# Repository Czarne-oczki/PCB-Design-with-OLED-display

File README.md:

# PCB Design with OLED display
# Overview
I am designing a 2-layer PCB that controls an OLED display via I2C, an SD card via SPI, and using a USB interface.

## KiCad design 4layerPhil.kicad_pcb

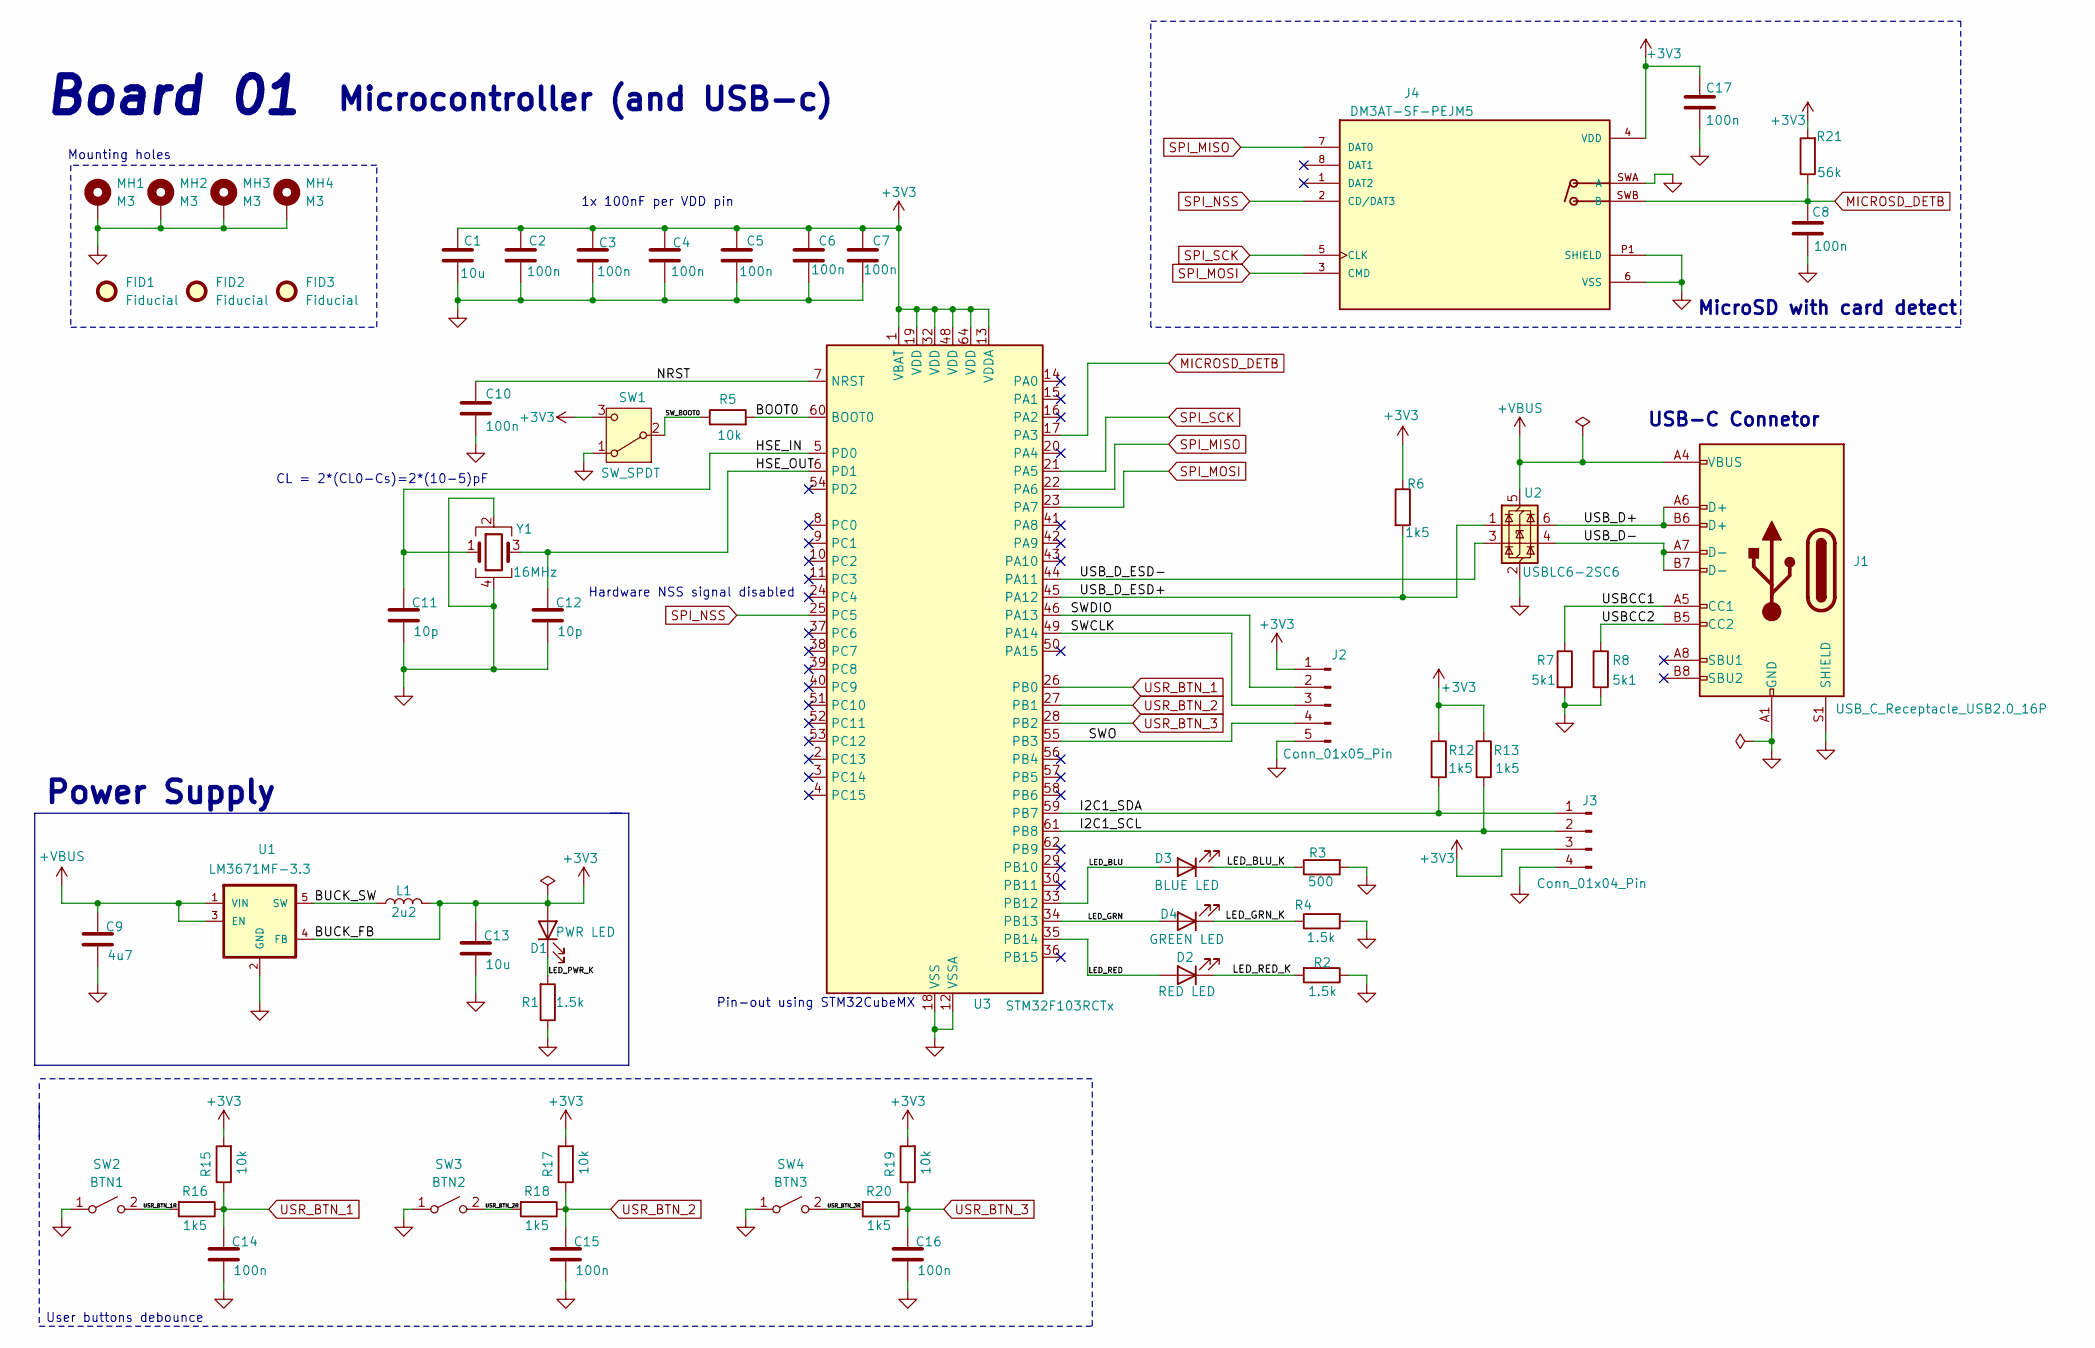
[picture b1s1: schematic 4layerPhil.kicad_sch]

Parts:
C1, C13: 10u; C_0805_2012Metric
C2, C3, C4, C5, C6, C7, C8, C10, C14, C15, C16, C17: 100n; C_0603_1608Metric
C9: 4u7; C_0805_2012Metric
C11, C12: 10p; C_0603_1608Metric
D1: PWR LED; LED_0603_1608Metric
D2: RED LED; LED_0603_1608Metric
D3: BLUE LED; LED_0603_1608Metric
D4: GREEN LED; LED_0603_1608Metric
FID1, FID2, FID3: Fiducial; Fiducial_1mm_Mask2mm
J1: USB_C_Receptacle_USB2.0_16P; USB_C_Receptacle_GCT_USB4105-xx-A_16P_TopMnt_Horizontal
J2: Conn_01x05_Pin; PinHeader_1x05_P2.54mm_Vertical
J3: Conn_01x04_Pin; PinHeader_1x04_P2.54mm_Vertical
J4: DM3AT-SF-PEJM5; HRS_DM3AT-SF-PEJM5; PARTREV 20200913
L1: 2u2; L_0805_2012Metric
MH1, MH2, MH3, MH4: M3; MountingHole_3.2mm_M3_Pad_Via
R1, R2, R4: 1.5k; R_0603_1608Metric
R3: 500; R_0603_1608Metric
R5, R15, R17, R19: 10k; R_0603_1608Metric
R6, R12, R13, R16, R18, R20: 1k5; R_0603_1608Metric
R7, R8: 5k1; R_0603_1608Metric
R21: 56k; R_0603_1608Metric
SW1: SW_SPDT; SW_SPDT_PCM12
SW2: BTN1; SW_SPST_TL3305C
SW3: BTN2; SW_SPST_TL3305C
SW4: BTN3; SW_SPST_TL3305C
U1: LM3671MF-3.3; SOT95P280X145-5N
U2: USBLC6-2SC6; SOT-23-6
U3: STM32F103RCTx; LQFP-64_10x10mm_P0.5mm
Y1: 16MHz; Crystal_SMD_3225-4Pin_3.2x2.5mm

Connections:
+3V3: C1.1, C2.1, C3.1, C4.1, C5.1, C6.1, C7.1, C13.1, C17.1, D1.2 (A), J2.1, J3.3, J4.4 (VDD), L1.2, R6.1, R12.1, R13.1, R15.2, R17.2, R19.2, R21.2, SW1.3 (C), U1.4 (FB), U3.1 (VBAT), U3.13 (VDDA), U3.19 (VDD), U3.32 (VDD), U3.48 (VDD), U3.64 (VDD)
+VBUS: C9.1, J1.A4 (VBUS), J1.A9 (VBUS), J1.B4 (VBUS), J1.B9 (VBUS), U1.1 (VIN), U1.3 (EN), U2.5 (VBUS)
/BOOT0: R5.2, U3.60 (BOOT0)
/BUCK_SW: L1.1, U1.5 (SW)
/HSE_IN: C11.1, U3.5 (PD0), Y1.1
/HSE_OUT: C12.1, U3.6 (PD1), Y1.3
/I2C1_SCL: J3.2, R13.2, U3.61 (PB8)
/I2C1_SDA: J3.1, R12.2, U3.59 (PB7)
/LED_BLU: D3.2 (A), U3.33 (PB12)
/LED_BLU_K: D3.1 (K), R3.1
/LED_GRN: D4.2 (A), U3.34 (PB13)
/LED_GRN_K: D4.1 (K), R4.1
/LED_PWR_K: D1.1 (K), R1.2
/LED_RED: D2.2 (A), U3.35 (PB14)
/LED_RED_K: D2.1 (K), R2.2
/NRST: C10.1, U3.7 (NRST)
/SWCLK: J2.3, U3.49 (PA14)
/SWDIO: J2.2, U3.46 (PA13)
/SWO: J2.4, U3.55 (PB3)
/SW_BOOT0: R5.1, SW1.2 (B)
/USBCC1: J1.A5 (CC1), R7.1
/USBCC2: J1.B5 (CC2), R8.1
/USB_D+: J1.A6 (D+), J1.B6 (D+), U2.6 (I/O1)
/USB_D-: J1.A7 (D-), J1.B7 (D-), U2.4 (I/O2)
/USB_D_ESD+: R6.2, U2.1 (I/O1), U3.45 (PA12)
/USB_D_ESD-: U2.3 (I/O2), U3.44 (PA11)
/USR_BTN_1R: R16.2, SW2.2 (B)
/USR_BTN_2R: R18.2, SW3.2 (B)
/USR_BTN_3R: R20.2, SW4.2 (B)
GND: C1.2, C2.2, C3.2, C4.2, C5.2, C6.2, C7.2, C8.2, C9.2, C10.2, C11.2, C12.2, C13.2, C14.2, C15.2, C16.2, C17.2, J1.A1 (GND), J1.A12 (GND), J1.B1 (GND), J1.B12 (GND), J1.S1 (SHIELD), J2.5, J3.4, J4.6 (VSS), J4.P1 (SHIELD), J4.P2 (SHIELD), J4.P3 (SHIELD), J4.P4 (SHIELD), J4.SWA (A), MH1.1, MH2.1, MH3.1, MH4.1, R1.1, R2.1, R3.2, R4.2, R7.2, R8.2, SW1.1 (A), SW2.1 (A), SW3.1 (A), SW4.1 (A), U1.2 (GND), U2.2 (GND), U3.12 (VSSA), U3.18 (VSS), U3.31 (VSS), U3.47 (VSS), U3.63 (VSS), Y1.2, Y1.4
MICROSD_DETB: C8.1, J4.SWB (B), R21.1, U3.17 (PA3)
SPI_MISO: J4.7 (DAT0), U3.22 (PA6)
SPI_MOSI: J4.3 (CMD), U3.23 (PA7)
SPI_NSS: J4.2 (CD/DAT3), U3.25 (PC5)
SPI_SCK: J4.5 (CLK), U3.21 (PA5)
USR_BTN_1: C14.1, R15.1, R16.1, U3.26 (PB0)
USR_BTN_2: C15.1, R17.1, R18.1, U3.27 (PB1)
USR_BTN_3: C16.1, R19.1, R20.1, U3.28 (PB2)

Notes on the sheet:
Hardware NSS signal disabled
Mounting holes
USB-C Connetor
CL = 2*(CL0-Cs)=2*(10-5)pF
User buttons debounce
1x 100nF per VDD pin
Board 01
Power Supply
Microcontroller (and USB-c)
Pin-out using STM32CubeMX
MicroSD with card detect

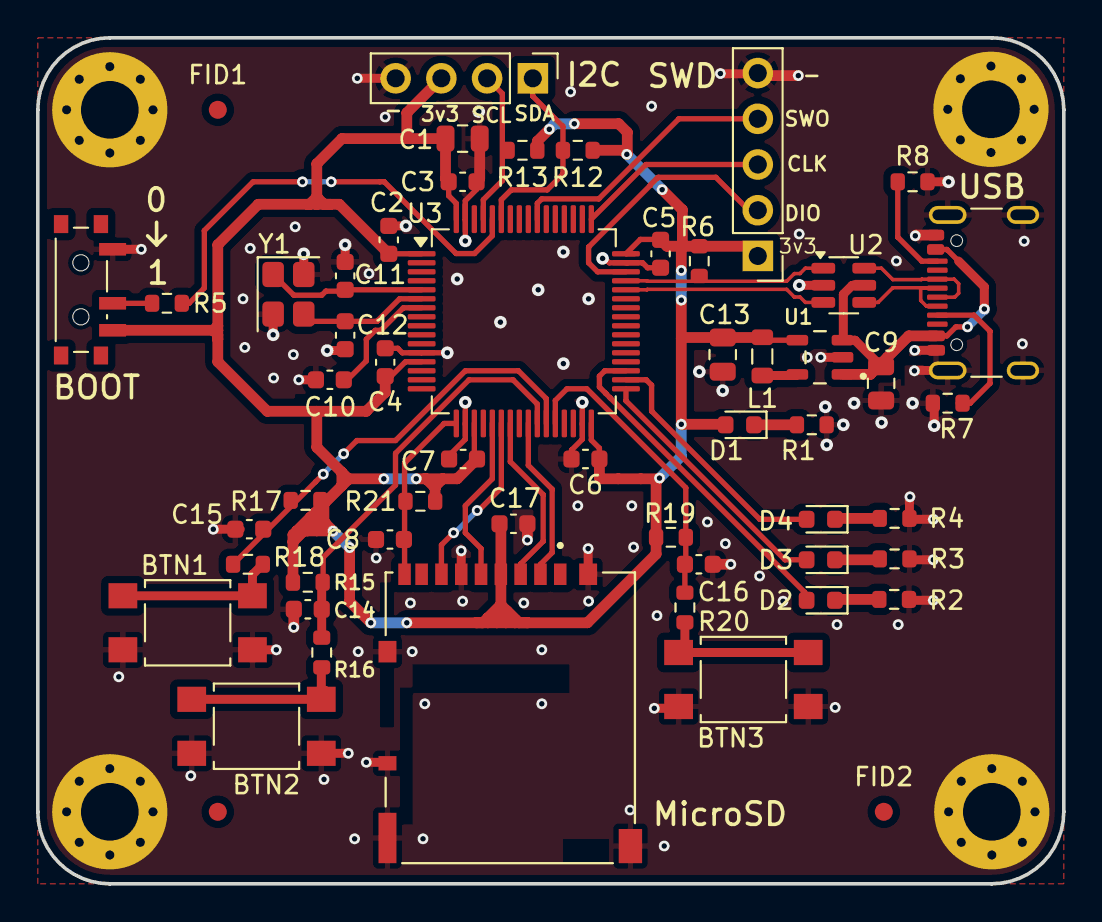
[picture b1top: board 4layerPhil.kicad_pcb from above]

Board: 2 copper layers, 57.0 x 47.0 mm, 58 parts (0 on the bottom side), 38 nets.

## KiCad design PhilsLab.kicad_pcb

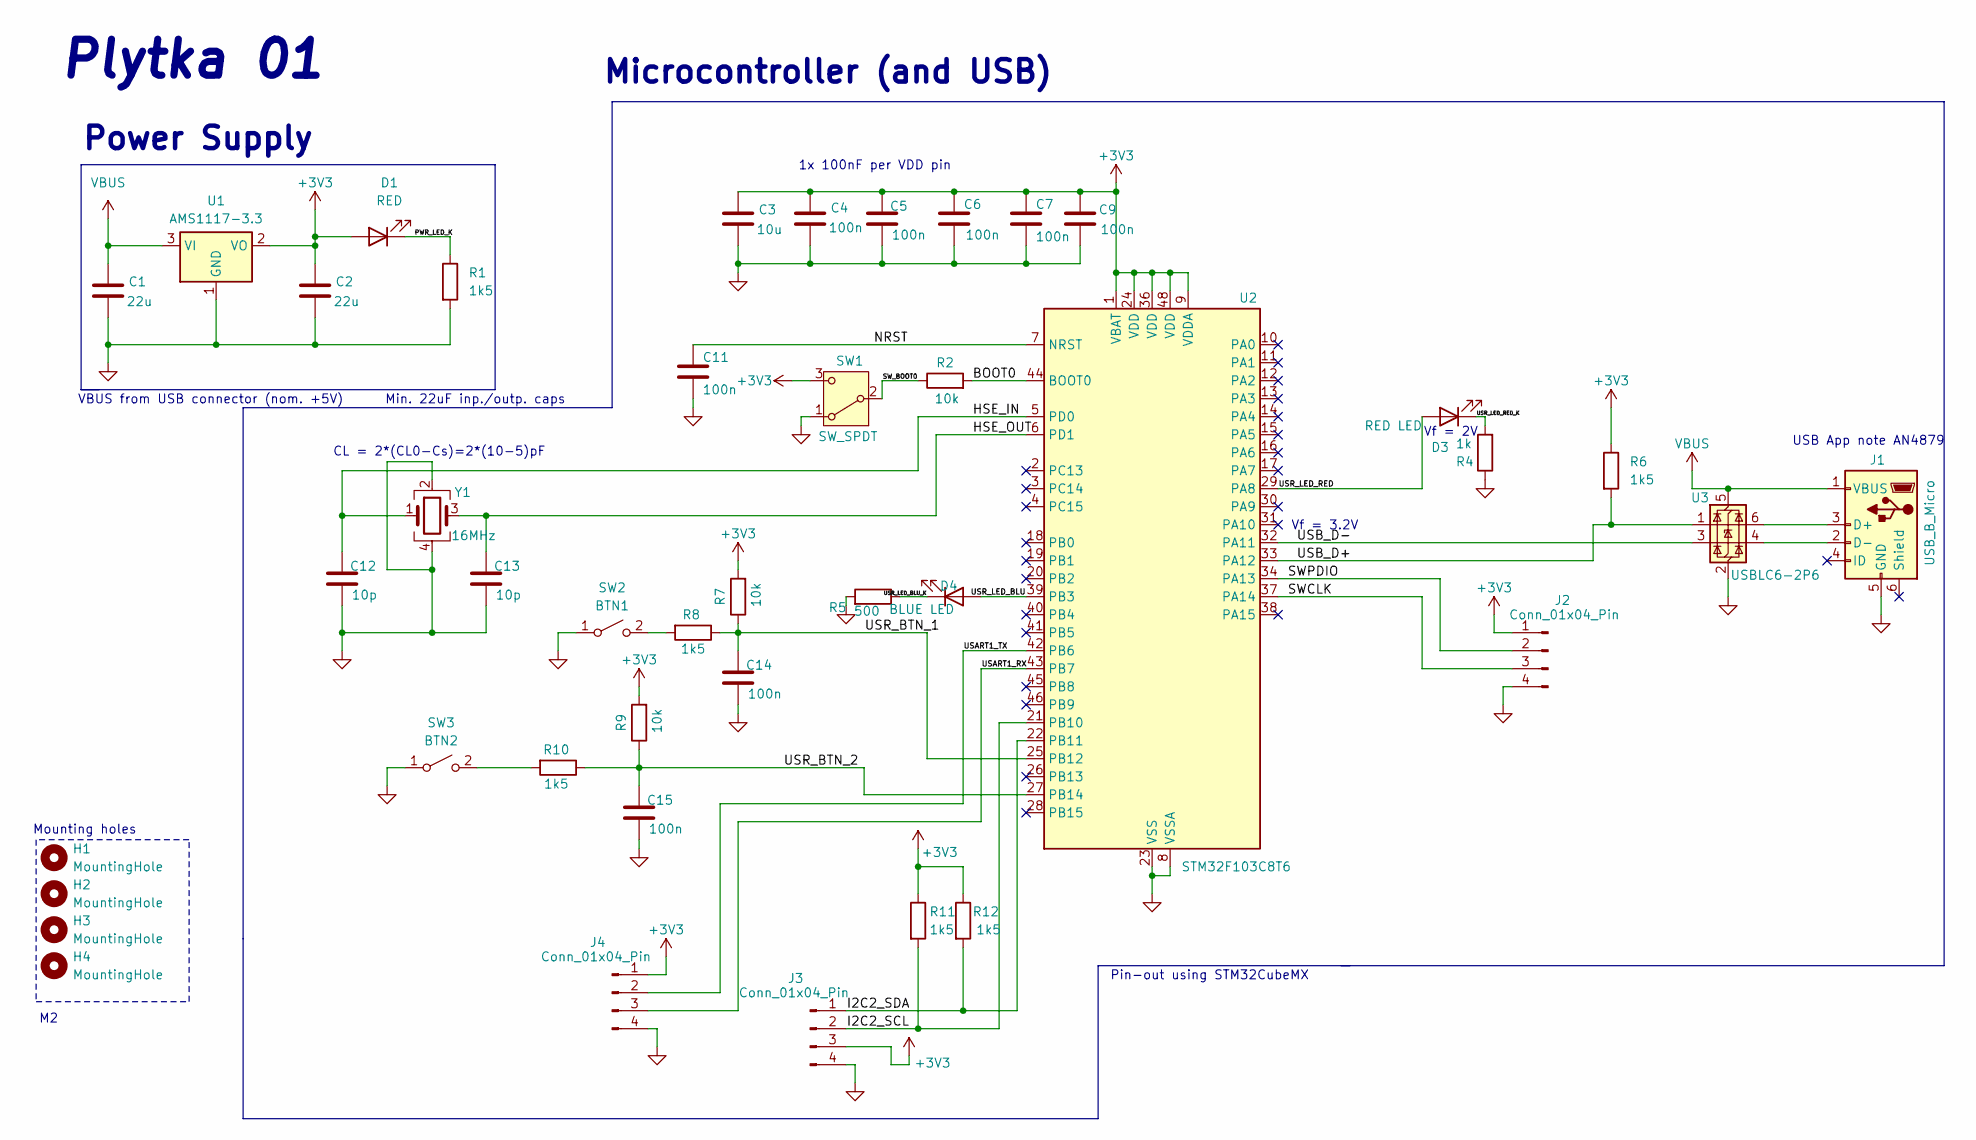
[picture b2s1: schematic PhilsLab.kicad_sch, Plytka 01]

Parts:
C1, C2: 22u; C_0805_2012Metric
C3: 10u; C_0603_1608Metric
C4, C5, C6, C7, C9, C11, C14, C15: 100n; C_0603_1608Metric
C12, C13: 10p; C_0603_1608Metric
D1: RED; LED_0603_1608Metric
D3: RED LED; LED_0603_1608Metric
D4: BLUE LED; LED_0603_1608Metric
H1, H2, H3, H4: MountingHole; MountingHole_2.2mm_M2
J1: USB_B_Micro; USB_Micro-B_Wuerth_629105150521
J2, J3, J4: Conn_01x04_Pin; PinHeader_1x04_P2.54mm_Vertical
R1, R6, R8, R10, R11, R12: 1k5; R_0603_1608Metric
R2, R7, R9: 10k; R_0603_1608Metric
R4: 1k; R_0603_1608Metric
R5: 500; R_0603_1608Metric
SW1: SW_SPDT; SW_SPDT_PCM12
SW2: BTN1; SW_SPST_TL3305C
SW3: BTN2; SW_SPST_TL3305C
U1: AMS1117-3.3; SOT-223-3_TabPin2
U2: STM32F103C8T6; LQFP-48_7x7mm_P0.5mm
U3: USBLC6-2P6; SOT-666
Y1: 16MHz; Crystal_SMD_3225-4Pin_3.2x2.5mm

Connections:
+3V3: C2.1, C3.1, C4.1, C5.1, C6.1, C7.1, C9.1, D1.2 (A), J2.1, J3.3, J4.1, R6.1, R7.2, R9.2, R11.1, R12.1, SW1.3 (C), U1.2 (VO), U2.1 (VBAT), U2.9 (VDDA), U2.24 (VDD), U2.36 (VDD), U2.48 (VDD)
/BOOT0: R2.2, U2.44 (BOOT0)
/HSE_IN: C12.1, U2.5 (PD0), Y1.1
/HSE_OUT: C13.1, U2.6 (PD1), Y1.3
/I2C2_SCL: J3.2, R11.2, U2.21 (PB10)
/I2C2_SDA: J3.1, R12.2, U2.22 (PB11)
/NRST: C11.1, U2.7 (NRST)
/PWR_LED_K: D1.1 (K), R1.1
/SWCLK: J2.3, U2.37 (PA14)
/SWPDIO: J2.2, U2.34 (PA13)
/SW_BOOT0: R2.1, SW1.2 (B)
/USART1_RX: J4.3, U2.43 (PB7)
/USART1_TX: J4.2, U2.42 (PB6)
/USB_D+: R6.2, U2.33 (PA12), U3.1 (I/O1)
/USB_D-: U2.32 (PA11), U3.3 (I/O2)
/USR_BTN_1: C14.1, R7.1, R8.1, U2.25 (PB12)
/USR_BTN_2: C15.1, R9.1, R10.1, U2.27 (PB14)
/USR_LED_BLU: D4.2 (A), U2.39 (PB3)
/USR_LED_BLU_K: D4.1 (K), R5.1
/USR_LED_RED: D3.2 (A), U2.29 (PA8)
/USR_LED_RED_K: D3.1 (K), R4.2
GND: C1.2, C2.2, C3.2, C4.2, C5.2, C6.2, C7.2, C9.2, C11.2, C12.2, C13.2, C14.2, C15.2, J1.5 (GND), J2.4, J3.4, J4.4, R1.2, R4.1, R5.2, SW1.1 (A), SW2.1 (A), SW3.1 (A), U1.1 (GND), U2.8 (VSSA), U2.23 (VSS), U2.35 (VSS), U2.47 (VSS), U3.2 (GND), Y1.2, Y1.4
unnamed: J1.3 (D+), U3.6 (I/O1)
unnamed: J1.2 (D-), U3.4 (I/O2)
unnamed: R8.2, SW2.2 (B)
unnamed: R10.2, SW3.2 (B)
VBUS: C1.1, J1.1 (VBUS), U1.3 (VI), U3.5 (VBUS)

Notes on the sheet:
1x 100nF per VDD pin
Pin-out using STM32CubeMX
Plytka 01
CL = 2*(CL0-Cs)=2*(10-5)pF
Vf = 2V
Vf = 3.2V
VBUS from USB connector (nom. +5V)
USB App note AN4879
Microcontroller (and USB)
Power Supply
Min. 22uF inp./outp. caps
Mounting holes

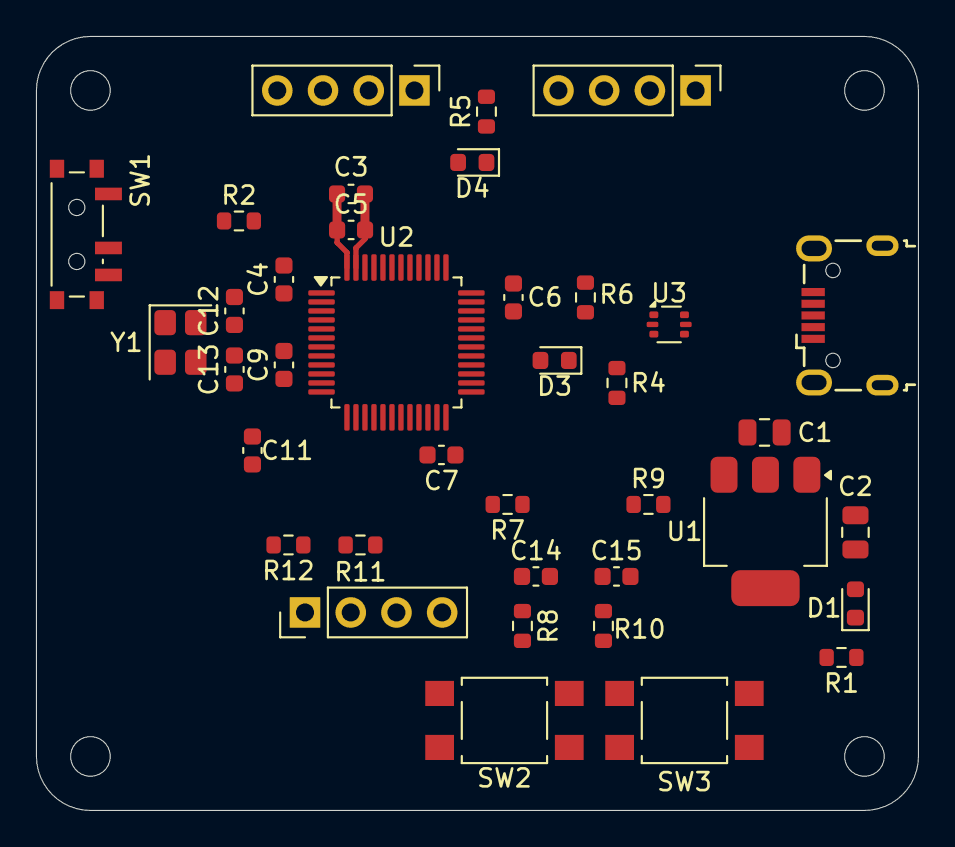
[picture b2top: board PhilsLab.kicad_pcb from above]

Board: 2 copper layers, 49.0 x 43.0 mm, 42 parts (0 on the bottom side), 27 nets.
